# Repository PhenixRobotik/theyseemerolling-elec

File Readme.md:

# Électronique pour "They see me rolling",  la base roulante de PhenixRobotik.

<div class="alert alert-warning">
    This project requires KiCAD 5.0 and is not compatible with previous versions (software and libraries).
</div>

* Stm32f3 (?)
  * Voltage instrumentation (power, digital)
  * Power current instrumentation

* IOs :
  * Power alimentation
  * Digital alimentation
  * JTAG debug (daisy-chain)
  * CAN Bus (daisy-chain)
  * UART ?

* 2 roues codeuses + 2 encodeurs rotatifs :
  * (suggestion salamandar) [Broadcom AS22-M570-xxxx](https://www.mouser.fr/ProductDetail/Broadcom/AS22-M570-4U14?qs=sGAEpiMZZMv5XWiOWIxhpE0U2KVVcWxhLQCaHpWVRl3ZAkIMm6c4WA%3d%3d)
    * Ø22mm × 10.9mm
    * 360 cpr to 2048 cpr
    * dual-channel + index channel
    * 5V

* 2 moteurs Maxon DC + 2 encodeurs rotatifs

* Driver moteurs
  * (suggestion salamandar) [ST L6207](http://www.st.com/content/st_com/en/products/motor-drivers/brushed-dc-motor-drivers/l6207.html)
    * POWERSO36
    * Operating supply voltage from 8 to 52 V
    * 5.6 A output peak current (2.8 A DC)
    * PWM current controllers
    * Operating frequency up to 100 KHz
    
* Current measurement
    * torque estimation / control
    * Way of doing it : Use a driver which provides this feature / shunt resistor / Hall effect sensor ?
    
* Architecture:
    * One single PCB card
    * One motor driver card (speed + torque control) + one position (+ odometrie ?) card ( = carte kiwi ?)
    * Two motor driver cards (speed + torque control) + one position (+ odometrie ?) card ( = carte kiwi ?)

## Eventually :

* IMU / 9-axes
* ...

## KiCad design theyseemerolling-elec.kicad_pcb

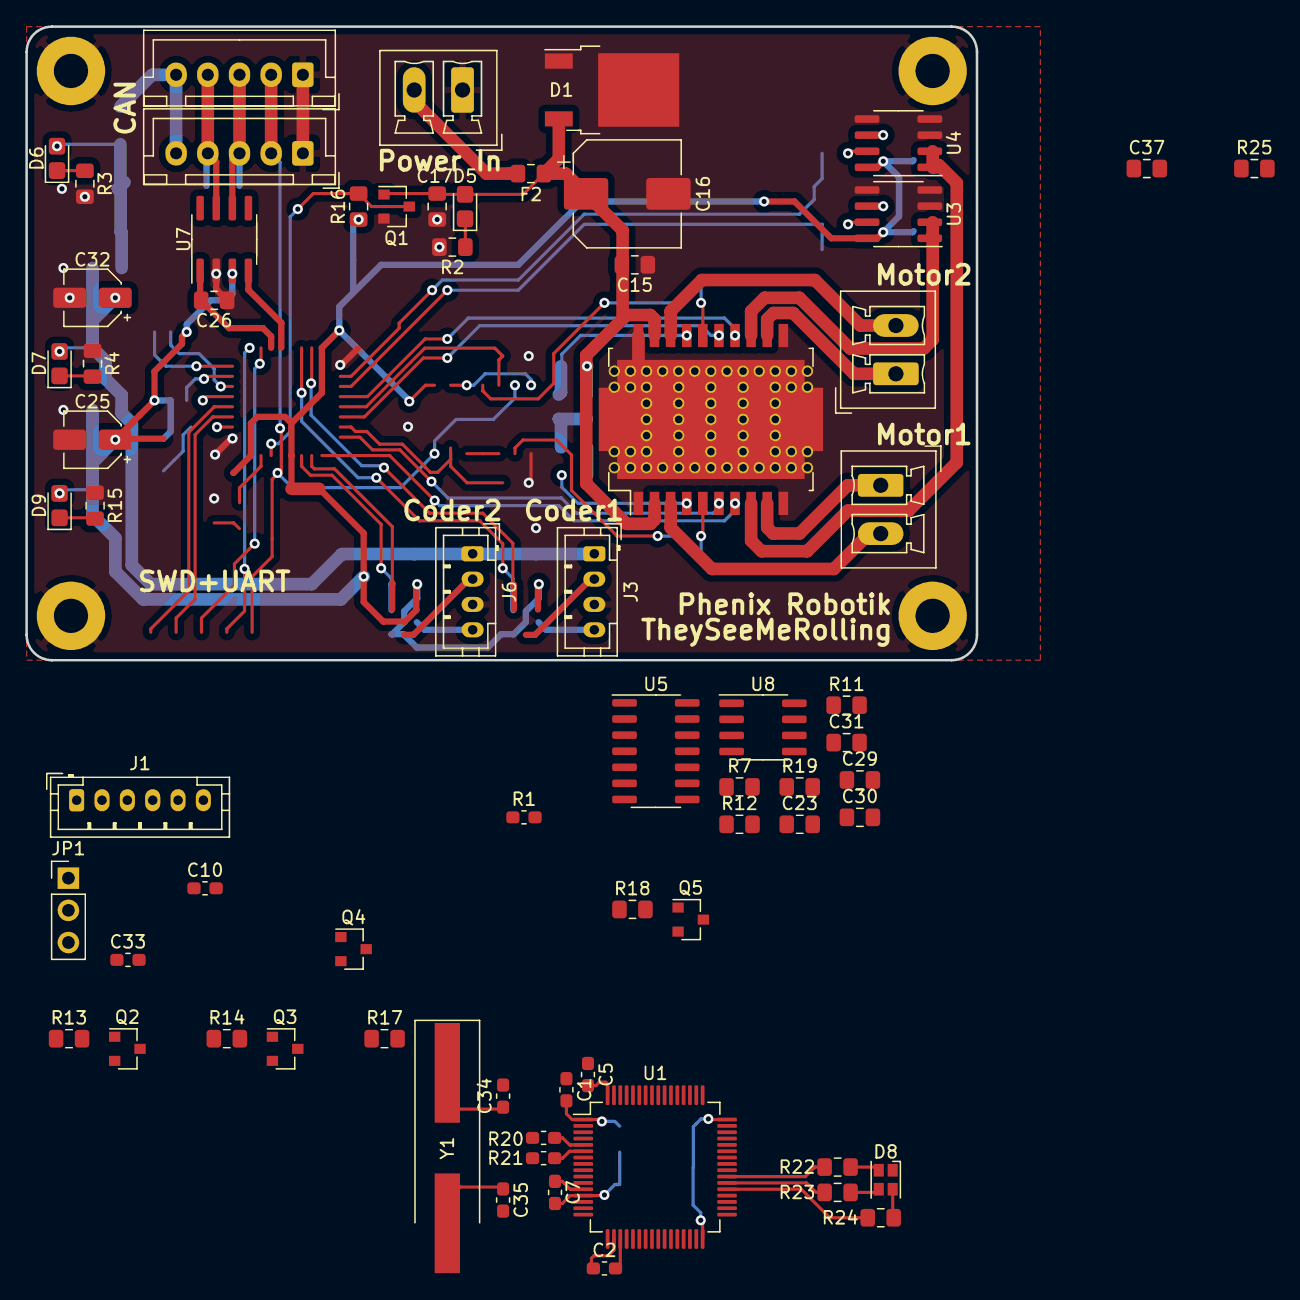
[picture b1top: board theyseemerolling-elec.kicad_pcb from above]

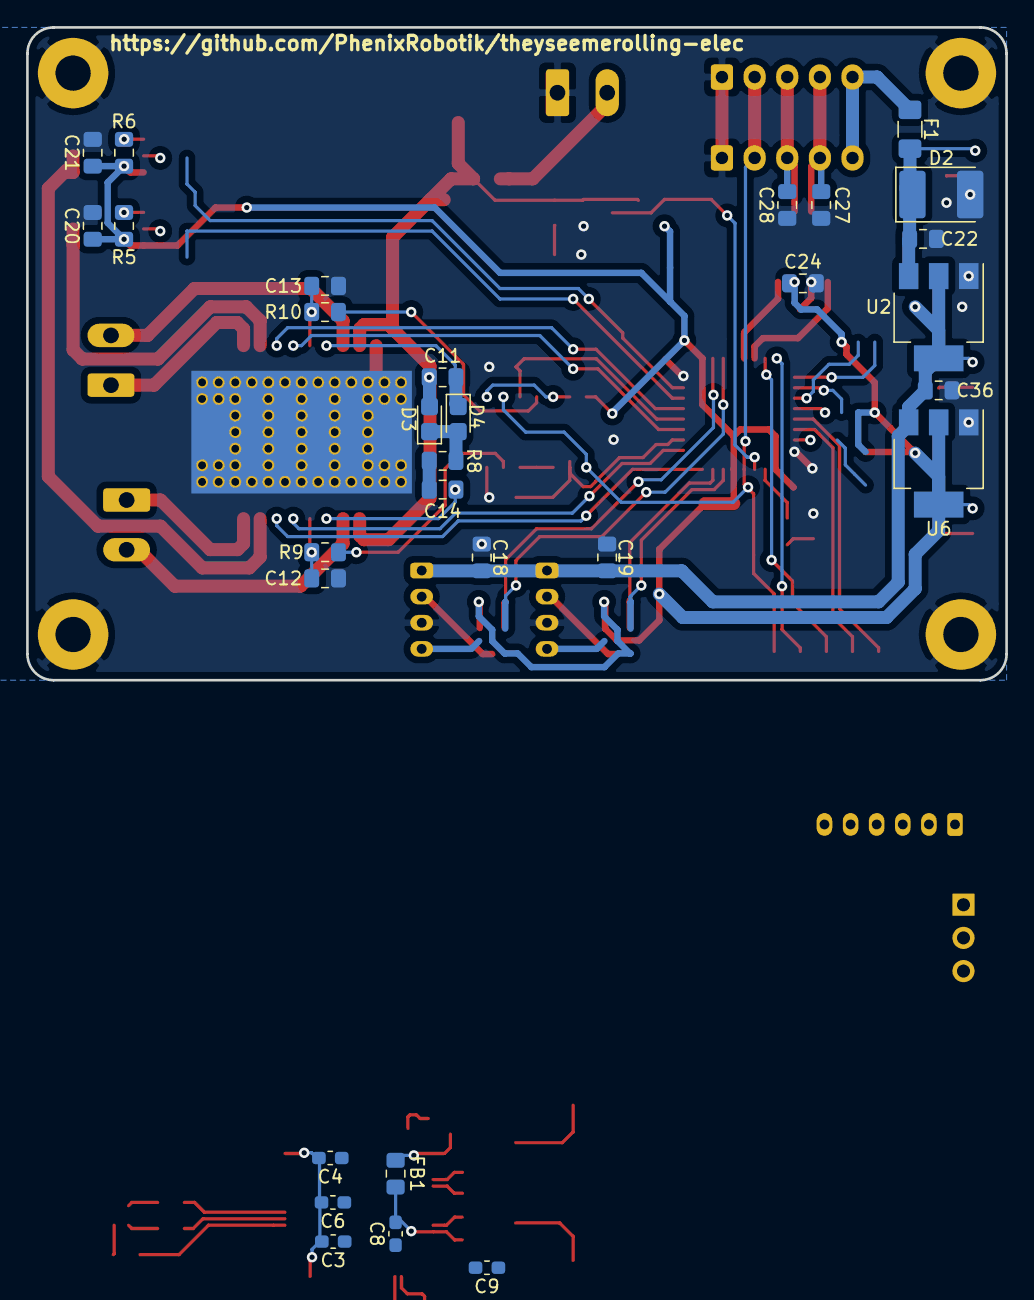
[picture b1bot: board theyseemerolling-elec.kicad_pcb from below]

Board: 2 copper layers, 75.0 x 50.0 mm, 102 parts (30 on the bottom side), 73 nets.

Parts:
C1, C2, C3, C4, C5, C7, C9: 100n; C_0603_1608Metric_Pad1.05x0.95mm_HandSolder
C6: 4.7u -- 10u; C_0603_1608Metric_Pad1.05x0.95mm_HandSolder
C8: 1u; C_0603_1608Metric_Pad1.05x0.95mm_HandSolder
C10, C33: 2u2; C_0603_1608Metric_Pad1.05x0.95mm_HandSolder
C11: 220n; C_0805_2012Metric_Pad1.15x1.40mm_HandSolder
C12, C13: 5.6n; C_0805_2012Metric_Pad1.15x1.40mm_HandSolder
C14: 10n; C_0805_2012Metric_Pad1.15x1.40mm_HandSolder
C15, C22, C36: 100n; C_0805_2012Metric_Pad1.15x1.40mm_HandSolder
C16: 100u; CP_Elec_8x10
C17: C; C_0805_2012Metric_Pad1.15x1.40mm_HandSolder
C18, C19, C20, C21, C24, C30, C31: 100nF; C_0805_2012Metric_Pad1.15x1.40mm_HandSolder
C23, C29, C37: 1n; C_0805_2012Metric_Pad1.15x1.40mm_HandSolder
C25, C32: 10u; CP_Elec_4x5.4
C26, C27, C28: 100p; C_0805_2012Metric_Pad1.15x1.40mm_HandSolder
C34, C35: C; C_0603_1608Metric_Pad1.05x0.95mm_HandSolder
D1: D_Schottky_AAK; TO-252-2
D2: D; D_2114_3652Metric_Castellated
D3, D4: 1N4148; D_0805_2012Metric_Castellated
D5, D6, D7, D9: LED_ALT; LED_0805_2012Metric_Castellated
D8: LED_ARGB; LED_Cree-PLCC4_2x2mm_CW
F1: Polyfuse 2A; Fuse_1206_3216Metric_Pad1.42x1.75mm_HandSolder
F2: 5A; Fuse_0805_2012Metric_Pad1.15x1.40mm_HandSolder
FB1: Ferrite_Bead; L_0805_2012Metric_Pad1.15x1.40mm_HandSolder
IC2: L6205PD; ST_PowerSO-20_SlugDown_ThermalVias
J1: Conn_Debug; JST_PH_B6B-PH-K_1x06_P2.00mm_Vertical
J2: Conn_Power_In; PhoenixContact_MCV_1,5_2-G-3.81_1x02_P3.81mm_Vertical
J3: Conn_Encoder1; JST_PH_B4B-PH-K_1x04_P2.00mm_Vertical
J4: Conn_Mot1; PhoenixContact_MCV_1,5_2-G-3.81_1x02_P3.81mm_Vertical
J5: Conn_Mot2; PhoenixContact_MCV_1,5_2-G-3.81_1x02_P3.81mm_Vertical
J6: Conn_Encoder2; JST_PH_B4B-PH-K_1x04_P2.00mm_Vertical
J7, J8: CAN_conn; JST_XH_B05B-XH-A_1x05_P2.50mm_Vertical
JP1: JP_Select_Boot; PinHeader_1x03_P2.54mm_Vertical
MK1, MK2, MK3, MK4: MountingHole_Pad; MountingHole_2.7mm_M2.5_Pad
Q1, Q2, Q3, Q4, Q5: BSS138; SOT-23
R1: 10k; R_0603_1608Metric_Pad1.05x0.95mm_HandSolder
R2, R3, R4, R15: R_LED; R_0805_2012Metric_Pad1.15x1.40mm_HandSolder
R5, R6: 10k; R_0805_2012Metric_Pad1.15x1.40mm_HandSolder
R7, R16, R19: 10kR; R_0805_2012Metric_Pad1.15x1.40mm_HandSolder
R8: 100R; R_0805_2012Metric_Pad1.15x1.40mm_HandSolder
R9, R10: 100k; R_0805_2012Metric_Pad1.15x1.40mm_HandSolder
R11, R12, R25: Rsense; R_0805_2012Metric_Pad1.15x1.40mm_HandSolder
R13, R14, R17, R18: R; R_0805_2012Metric_Pad1.15x1.40mm_HandSolder
R20, R21: R; R_0603_1608Metric_Pad1.05x0.95mm_HandSolder
R22: 39; R_0805_2012Metric_Pad1.15x1.40mm_HandSolder
R23: 27; R_0805_2012Metric_Pad1.15x1.40mm_HandSolder
R24: 91; R_0805_2012Metric_Pad1.15x1.40mm_HandSolder
U1: STM32F405RGTx; LQFP-64_10x10mm_P0.5mm
U2: LD1117S50TR_SOT223; SOT-223-3_TabPin2
U3, U4: ACS711xLCTR-12AB; SOIC-8_3.9x4.9mm_P1.27mm
U5: 74HC00; SOIC-14_3.9x8.7mm_P1.27mm
U6: LD1117S33TR_SOT223; SOT-223-3_TabPin2
U7: TCAN332; SOIC-8_3.9x4.9mm_P1.27mm
U8: AT25SF041; SOIC-8_3.9x4.9mm_P1.27mm
Y1: 8Mhz; Crystal_SMD_HC49-SD_HandSoldering

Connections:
+3V3: C1.2, C2.2, C3.2, C4.2, C5.2, C6.2, C20.2, C21.2, C24.1, C25.1, C30.2, C31.1, D8.1, D9.2, FB1.1, JP1.3, Q2.1, Q3.1, Q4.1, Q5.1, R5.1, R6.1, R13.1, R14.1, R16.1, R17.1, R18.1, U1.1, U1.19, U1.32, U1.48, U1.64, U3.8, U4.8, U5.14, U6.2, U7.3, U8.3, U8.7, U8.8
+5V: C18.1, C19.1, C32.1, C36.1, D7.2, J3.1, J6.1, U2.2, U6.3
/CAN/+7V_CAN: F1.2, J7.5, J8.5
/CAN/CAN_RX: U1.44, U7.4
/CAN/CAN_TX: C26.1, U1.45, U7.1
/CAN/NRST: J7.2, J8.2
/DualDCDriver/EN_A: R9.2, U1.23
/DualDCDriver/EN_B: R10.2, U1.27
/DualDCDriver/IN1_A: IC2.6, U1.22
/DualDCDriver/IN1_B: IC2.14, U1.26
/DualDCDriver/IN2_A: IC2.7, U1.21
/DualDCDriver/IN2_B: IC2.15, U1.28
/DualDCDriver/M1+: IC2.9, J4.1
/DualDCDriver/M1-: IC2.3, J4.2
/DualDCDriver/M2+: IC2.12, J5.1
/DualDCDriver/M2-: IC2.18, J5.2
/DualDCDriver/Sense_A: C29.1, R11.1, R25.2, U1.24
/DualDCDriver/Sense_A_Fault: R6.2, U4.6
/DualDCDriver/Sense_A_Filtered: C37.1, R11.2
/DualDCDriver/Sense_B: C23.1, R12.2, U1.25
/DualDCDriver/Sense_B_Fault: R5.2, U3.6
/DualDCDriver/Sheet5D536196/Input: IC2.8, U4.1, U4.2
/DualDCDriver/sheet5D55A35B/Input: IC2.13, U3.1, U3.2
/EN_A_and_NRST: R19.2, U5.2
/EN_B_and_NRST: R7.1, U5.10
/nrst: U5.1, U5.9
/shift_enc1A/Input: J3.2, Q2.3
/shift_enc1B/Input: J3.4, Q5.3
/shift_enc2A/Input: J6.2, Q3.3
/shift_enc2B/Input: J6.4, Q4.3
/stm32f4/Encoder_1_A: Q5.2, R18.2, U1.41
/stm32f4/Encoder_1_B: Q2.2, R13.2, U1.42
/stm32f4/Encoder_2_A: Q3.2, R14.2, U1.14
/stm32f4/Encoder_2_B: Q4.2, R17.2, U1.15
/stm32f4/SWDCLK: J1.3, U1.49
/stm32f4/SWDIO: J1.4, U1.46
/stm32f4/nrst: C9.2, J1.2, U1.7
/stm32f4/~AboutDaPower: Q1.3, R16.2
GND: C1.1, C2.1, C3.1, C4.1, C5.1, C6.1, C7.1, C8.1, C9.1, C10.2, C12.2, C13.2, C15.2, C16.2, C17.2, C18.2, C19.2, C20.1, C21.1, C22.2, C23.2, C24.2, C25.2, C26.2, C27.1, C28.2, C29.2, C30.1, C31.2, C32.2, C33.2, C34.2, C35.2, C36.2, C37.2, D1.1, D1.2, D2.2, IC2.1, IC2.10, IC2.11, IC2.20, IC2.21, J1.1, J2.1, J3.3, J6.3, J7.1, J8.1, JP1.1, MK1.1, MK2.1, MK3.1, MK4.1, Q1.2, R2.2, R3.2, R4.2, R7.2, R15.2, R19.1, U1.12, U1.18, U1.63, U2.1, U3.3, U3.4, U3.5, U4.3, U4.4, U4.5, U5.7, U6.1, U7.2, U8.4
unnamed: C10.1, U1.31
unnamed: C11.2, D4.1, IC2.17
unnamed: C12.1, IC2.5, R9.1
unnamed: C13.1, IC2.16, R10.1
unnamed: C14.1, IC2.4
unnamed: C14.2, R8.1
unnamed: C22.1, D2.1, D6.2, F1.1, U2.3
unnamed: C27.2, J7.4, J8.4, U7.7
unnamed: C28.1, J7.3, J8.3, U7.6
unnamed: C33.1, U1.47
unnamed: C34.1, R20.2, Y1.1
unnamed: C35.1, R21.2, Y1.2
unnamed: D3.1, D4.2, R8.2
unnamed: D5.1, R2.1
unnamed: D6.1, R3.1
unnamed: D7.1, R4.1
unnamed: D8.2, R24.1
unnamed: D8.3, R23.1
unnamed: D8.4, R22.1
unnamed: D9.1, R15.1
unnamed: F2.2, J2.2
unnamed: JP1.2, R1.2
unnamed: R1.1, U1.60
unnamed: R12.1, U3.7
unnamed: R20.1, U1.5
unnamed: R21.1, U1.6
unnamed: R22.2, U1.39
unnamed: R23.2, U1.38
unnamed: R24.2, U1.37
unnamed: R25.1, U4.7
unnamed: U5.3, U5.4, U5.5
unnamed: U5.8, U5.12, U5.13
VCC: C11.1, C15.1, C16.1, C17.1, D1.3, D3.2, D5.2, F2.1, IC2.2, IC2.19, Q1.1
VDDA: C7.2, C8.2, FB1.2, U1.13

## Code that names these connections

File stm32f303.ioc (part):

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Mcu.Name=STM32F303K(6-8)Tx
Mcu.Package=LQFP32
Mcu.UserName=STM32F303K8Tx
PA0.GPIOParameters=GPIO_Label
PA0.GPIO_Label=Encoder_2_B [TIM2_CH1]
PA0.Signal=S_TIM2_CH1_ETR
PA1.GPIOParameters=GPIO_Label
PA1.GPIO_Label=Encoder_2_A [TIM2_CH2]
PA1.Signal=S_TIM2_CH2
PA10.GPIOParameters=GPIO_Label
PA10.GPIO_Label=Sense_B_Fault
PA10.Signal=GPIO_Input
PA11.Mode=Master
PA11.Signal=CAN_RX
PA12.Mode=Master
PA12.Signal=CAN_TX
PA13.Mode=Serial_Wire
PA13.Signal=SYS_JTMS-SWDIO
PA14.Mode=Serial_Wire
PA14.Signal=SYS_JTCK-SWCLK
PA15.GPIOParameters=GPIO_Label
PA15.GPIO_Label=SPI1_CS
PA15.Signal=GPIO_Output
PA2.GPIOParameters=GPIO_Label
PA2.GPIO_Label=IN2_A
PA2.Signal=GPIO_Output
PA3.GPIOParameters=GPIO_Label
PA3.GPIO_Label=IN1_A
PA3.Signal=GPIO_Output
PA4.GPIOParameters=GPIO_Label
PA4.GPIO_Label=EN_A [TIM3_CH2]
PA4.Signal=S_TIM3_CH2
PA5.GPIOParameters=GPIO_Label
PA5.GPIO_Label=IN2_B
PA5.Signal=GPIO_Output
PA6.GPIOParameters=GPIO_Label
PA6.GPIO_Label=EN_B [TIM3_CH1]
PA6.Signal=S_TIM3_CH1
PA7.GPIOParameters=GPIO_Label
PA7.GPIO_Label=IN1_B
PA7.Signal=GPIO_Output
PA8.GPIOParameters=GPIO_Label
PA8.GPIO_Label=Encoder_1_A [TIM1_CH1]
PA8.Signal=S_TIM1_CH1
PA9.GPIOParameters=GPIO_Label
PA9.GPIO_Label=Encoder_1_B [TIM1_CH2]
PA9.Signal=S_TIM1_CH2
PB0.GPIOParameters=GPIO_Label
PB0.GPIO_Label=Sense_B_Filtered [ADC1_IN11]
PB0.Mode=IN11-Single-Ended
PB0.Signal=ADC1_IN11
PB1.GPIOParameters=GPIO_Label
PB1.GPIO_Label=Sense_A_Filtered [ADC1_IN12]
PB1.Mode=IN12-Single-Ended
PB1.Signal=ADC1_IN12
PB3.Mode=Full_Duplex_Master
PB3.Signal=SPI1_SCK
PB4.Mode=Full_Duplex_Master
PB4.Signal=SPI1_MISO
PB5.Mode=Full_Duplex_Master
PB5.Signal=SPI1_MOSI
PB6.Mode=Asynchronous
PB6.Signal=USART1_TX
PB7.Mode=Asynchronous
PB7.Signal=USART1_RX
PF0\ /\ OSC_IN.GPIOParameters=GPIO_Label
PF0\ /\ OSC_IN.GPIO_Label=LED
PF0\ /\ OSC_IN.Signal=GPIO_Output
PF1\ /\ OSC_OUT.GPIOParameters=GPIO_Label
PF1\ /\ OSC_OUT.GPIO_Label=POWER_PRESENCE
PF1\ /\ OSC_OUT.Signal=GPIO_Input
RCC.HSEPLLFreq_Value=8000000
RCC.HSE_VALUE=8000000
RCC.SYSCLKFreq_VALUE=8000000
board=custom

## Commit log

2018-05-22 Add KiCAD gitignore, Readme.md
2018-05-22 add st/tsop libs, basic kicad files.
2018-05-23 fix project
2018-05-23 Add DualDCDriver sub-schematics, with two designs.
2018-05-24 Add kicad version warning
2018-05-24 default-ly place component on pcb
2018-05-24 Add connectors for dummy pcb routing
2018-05-24 route L6205
2018-05-30 Remove lib subdir. Use phenix_kicad repository as submodule.
2018-06-09 Remove duplicates, remove motors and add connectors
2018-06-09 Fix sym lib table
2018-06-09 add fp-lib-table
2018-06-09 PCB: remove duplicate, add 10cm×5cm board outline
2018-06-10 f3 and current sensors added
2018-06-11 logic to stop motors in reset state and current sense filter
2018-06-11 input 7V 5V regulator
2018-06-12 CAN tranciever added and f3 wired
2018-06-17 JTAG pins and power presence
2018-06-17 forgot to connecte the led
2018-06-17 Fix can_conn usage
2018-09-28 change some symbol names for conformity
2018-09-28 update schemas, cleanup, renames
2018-09-28 Updated PCB. logic is almost done, power is left to do
2018-09-29 change connectors. Add swd.
2018-09-29 Change GNDD -> GND
2018-09-29 routing
2018-09-29 routing finished
2018-09-30 SPI flash added, JTAG removed, uart connector added
2018-09-30 move text
2018-10-01 clean libraries
2018-10-01 Remap STM32 with stm32cubemx
2018-10-01 update submodule
2018-10-01 Use molex connectors
2018-10-02 Set footprints, values for capas
2018-10-02 add mounting holes
2018-10-03 Use correct footprints, merge uart + swd connectors
2018-10-03 PCB refactored, down to 80mm, correct footprints.
2018-10-03 Finished board, kinda cleaned up
2018-10-03 decouplage des alims
2018-10-03 Fix CAN_conn
2018-10-03 cleanup pcb, reorganize text
2018-10-03 Add text and logos
2018-10-07 rename components
2018-10-07 Change connectors for JST
2018-10-07 Use JST_PH connectors for encoders. Re-route with new connectors.
2018-10-08 Add script to autogenerate gerber zip. update submodule.
2018-10-08 autodetect kicad_pcb file
2018-10-10 level conversion, to check and route
2018-10-10 correction, to route
2018-10-13 Added BSS138 on MCP2551, need to route
2018-10-13 Fixed mounting holes schematic
2018-10-13 footprint 0805
2018-10-20 Schematic modifications, to be checked
2018-10-20 Updated cubemx pins configuration
2018-10-20 Library update
2018-10-20 fix libraries
2018-10-21 Change CAN driver for 3v3 compliancy.
2018-10-21 Start to put components on both sides
2018-10-28 update schema, pcb, use double face components, tht jumper.
2018-11-01 Rename schema library
2018-11-01 Use new footprint
2018-11-01 Update from pcb after symbol changes
2018-11-01 update gitignore and phenix_kicad
2018-11-01 update sym libs
2018-11-01 update pcb a bit
2018-11-02 Rename PhoenixRobotik as PhenixRobotik
2018-11-02 remove wire
2018-11-02 Fusionner les segments superposés
2018-11-04 change components
2018-11-04 prettier
2018-11-04 Références
2018-11-04 Add text
2018-11-04 Change connectors. reduce size.
2018-11-05 fix phoenix/phenix
2018-11-05 Fix : use new footprints
2018-11-05 Cleanup, check footprints, connect mounting holes to GND
2018-11-05 Move silkscreen
2018-11-07 Changed fuse footprint
2018-11-09 Fix footprint on pcb
2019-03-31 Add maxon PCB for motor
2019-08-09 Some rewrite, prepare stm32f405
2019-08-10 Rework the schematics. Destroy the pcb. re-annotated the schematics.
2019-08-10 add correct rgb led
2019-08-10 refactoring
2019-11-05 continue stm32f405
2019-11-07 lib update
